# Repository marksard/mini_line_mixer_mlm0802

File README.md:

# Mini Line Mixer MLM0802

'Mini Line Mixer MLM0802' is 100mm x 100mm size audio line level mixer.  
A total of 3ch x2 of mono inputs and 1ch of stereo inupt, 2ch of stereo outputs are provided.  
This is perfect for mixing audio from small instruments.  
It does not have a pan pot, but can be used as a stereo 4-channel mixer.  

[blog](https://marksard.github.io/2023/02/23/make-line-mixer/)

## Specification

### Input

Monoral:  

- 3ch (A line group)  
- 3ch (B line group)  

3.5mm phone jack (TS, Unbaranced)

Stereo:  

- 1ch (Input as Tip to A line group, and as Ring to input B line group)  

3.5mm phone jack (TRS, Unbaranced)  

### Output

Monoral:  

- A output  
- B output  

3.5mm phone jack (TS, Unbaranced)  

Stereo:  

- Monitor output  

3.5mm phone jack (TRS, Unbaranced)  
The user can select A or B outputs for the left and right channels, respectively.  

### Power supply

- 5V to 9V
- MAX 100mA

### Block diagram

### Parts List

|Item|Qty|Reference(s)|Value|Part Model No.|
|:--|:--|:--|:--|:--|
|1|8|C1, C2, C3, C4, C5, C6, C7, C8|1u|サイズ max 5phi x 11mm|
|2|6|C9, C10, C12, C13, C15, C17|22p|セラミック seramic|
|3|2|C11, C14|47u|サイズ max 5phi x 11mm|
|4|2|C16, C18|470u|サイズ max 10phi x 12.5mm|
|5|1|C101|100u|サイズ max 10phi x 12.5mm|
|6|4|C102, C104, C105, C106|100n|積セラ multilayer ceramic|
|7|1|C103|47u|サイズ max 5phi x 11mm|
|8|1|J1|Ach1|マル信 est-marushin MJ-355W|
|9|1|J2|Ach2|マル信 est-marushin MJ-355W|
|10|1|J3|Ach3|マル信 est-marushin MJ-355W|
|11|1|J4|A/Bch4|マル信 est-marushin MJ-355W|
|12|1|J5|Bch1|マル信 est-marushin MJ-355W|
|13|1|J6|Bch2|マル信 est-marushin MJ-355W|
|14|1|J7|Bch3|マル信 est-marushin MJ-355W|
|15|1|J9|A Out|マル信 est-marushin MJ-355W|
|16|1|J10|B Out|マル信 est-marushin MJ-355W|
|17|1|J11|Phone Out|マル信 est-marushin MJ-355W|
|18|1|J101|Center negative|マル信 est-marushin MJ-179P|
|19|4|Q1, Q2, Q3, Q4|2SK170 or 2SK303L|2SK170 or 2SK303L|
|20|12|R1, R2, R3, R4, R5, R6, R7, R8, R12, R18, R22, R27|51k|金属皮膜 metal film 1/4w|
|21|4|R9, R15, R21, R26|1meg|金属皮膜 metal film 1/4w|
|22|4|R10, R11, R16, R17|27k|金属皮膜 metal film 1/4w|
|23|4|R14, R20, R25, R30|10k|金属皮膜 metal film 1/4w|
|24|2|R23, R28|20k|金属皮膜 metal film 1/4w|
|25|1|R101|1.5k|金属皮膜 metal film 1/4w|
|26|2|R102, R103|4.7k|金属皮膜 metal film 1/4w|
|27|6|RV1, RV2, RV3, RV5, RV6, RV7|A10k|ALPS RK09L1140-F15-C0-A103|
|28|1|RV4|A10k|ALPS RK09L1240-F15-C0-A103 2gang (2連)|
|29|2|RV9, RV10|B100k|ALPS RK09L1140-F15-C0-B104|
|30|1|RV11|B50k|ALPS RK09L1240-F15-C0-B503 2gang (2連)|
|31|1|SW1|Lch Selecter|NKK B-12CCPR|
|32|1|SW2|Rch Selecter|NKK B-12CCPR|
|33|1|SW101|Power Sw|NKK B-12CCPR|
|34|1|U1|NJM5532|NJM-5532|
|35|2|U2, U3|NJM5532|NJM-5532|
|36|4|-|-|Both Screw Spacer M3 11mm|
|37|8|-|-|Screw M3 4mm|
|38|4|-|-|Feet|
|39|10|-|Pot Knob|D-type 180digree<br>max outer size phi14mm|
|40|1|-|-|DC Adapter 9V 100mA Center negative, 2.1mm/5.5mm Jack|

### PCB image

### Schematic

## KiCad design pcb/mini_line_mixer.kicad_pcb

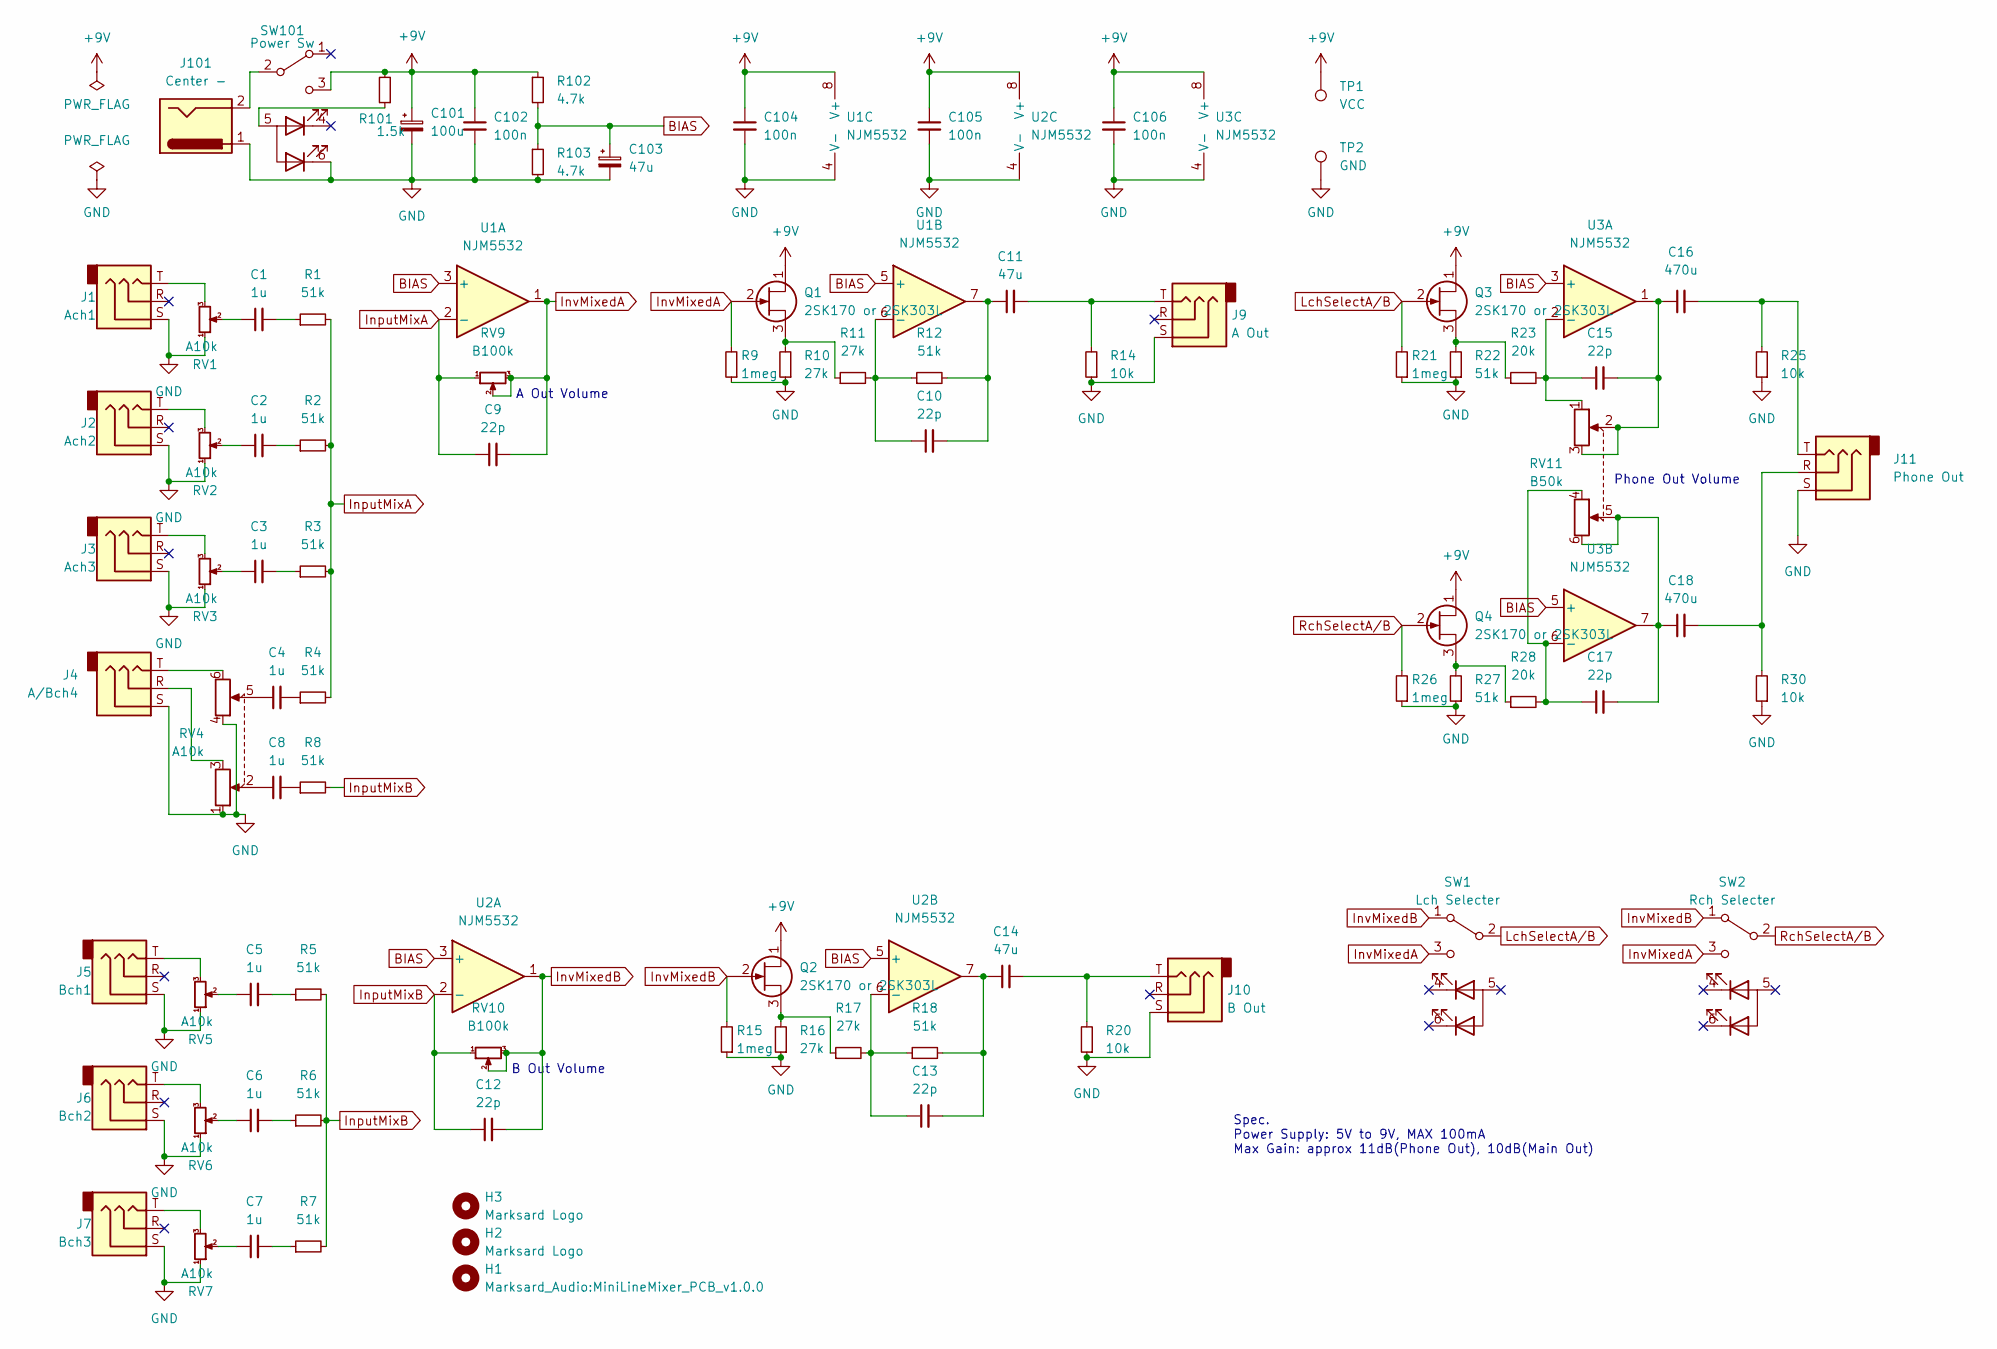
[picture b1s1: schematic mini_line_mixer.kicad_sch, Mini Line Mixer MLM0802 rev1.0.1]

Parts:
C1, C2, C3, C4, C5, C6, C7, C8: 1u; Capacitor_THT_5x11_Holizontal; Part Model No. サイズ max 5phi x 11mmまで
C9, C10, C12, C13, C15, C17: 22p; C_Disc_D4.7mm_W2.5mm_P5.00mm; Part Model No. セラミック seramic
C11, C14, C103: 47u; Capacitor_THT_5x11_Holizontal; Part Model No. サイズ max 5phi x 11mmまで
C16, C18: 470u; Capacitor_THT_10x12.5_Holizontal; Part Model No. サイズ max 10phi x 12.5mm
C101: 100u; Capacitor_THT_10x12.5_Holizontal; Part Model No. サイズ max 10phi x 12.5mm
C102, C104, C105, C106: 100n; Capacitor_THT_2.5_3.6_Ceramic; Part Model No. 積セラ multilayer ceramic
H1: Marksard_Audio:MiniLineMixer_PCB_v1.0.0; MiniLineMixer_PCB_v1.0.0
H2, H3: Marksard Logo; marksard_logo
J1: Ach1; MJ-355W; Part Model No. マル信 est-marushin MJ-355W
J2: Ach2; MJ-355W; Part Model No. マル信 est-marushin MJ-355W
J3: Ach3; MJ-355W; Part Model No. マル信 est-marushin MJ-355W
J4: A/Bch4; MJ-355W; Part Model No. マル信 est-marushin MJ-355W
J5: Bch1; MJ-355W; Part Model No. マル信 est-marushin MJ-355W
J6: Bch2; MJ-355W; Part Model No. マル信 est-marushin MJ-355W
J7: Bch3; MJ-355W; Part Model No. マル信 est-marushin MJ-355W
J9: A Out; MJ-355W; Part Model No. マル信 est-marushin MJ-355W
J10: B Out; MJ-355W; Part Model No. マル信 est-marushin MJ-355W
J11: Phone Out; MJ-355W; Part Model No. マル信 est-marushin MJ-355W
J101: Center -; MJ-179P; Part Model No. マル信 est-marushin MJ-179P
Q1, Q2, Q3, Q4: 2SK170 or 2SK303L; TO-92_K170-303L; Part Model No. 2SK170 or 2SK303L
R1, R2, R3, R4, R5, R6, R7, R8, R12, R18, R22, R27: 51k; R_Axial_DIN0204_L3.6mm_D1.6mm_P2.54mm_Vertical; Part Model No. 金属皮膜 metal film 1/4w
R9, R15, R21, R26: 1meg; R_Axial_DIN0204_L3.6mm_D1.6mm_P2.54mm_Vertical; Part Model No. 金属皮膜 metal film 1/4w
R10, R11, R16, R17: 27k; R_Axial_DIN0204_L3.6mm_D1.6mm_P2.54mm_Vertical; Part Model No. 金属皮膜 metal film 1/4w
R14, R20, R25, R30: 10k; R_Axial_DIN0204_L3.6mm_D1.6mm_P2.54mm_Vertical; Part Model No. 金属皮膜 metal film 1/4w
R23, R28: 20k; R_Axial_DIN0204_L3.6mm_D1.6mm_P2.54mm_Vertical; Part Model No. 金属皮膜 metal film 1/4w
R101: 1.5k; R_Axial_DIN0204_L3.6mm_D1.6mm_P2.54mm_Vertical; Part Model No. 金属皮膜 metal film 1/4w
R102, R103: 4.7k; R_Axial_DIN0204_L3.6mm_D1.6mm_P2.54mm_Vertical; Part Model No. 金属皮膜 metal film 1/4w
RV1, RV2, RV3, RV5, RV6, RV7: A10k; Potentiometer_THT_RK09L1140; Part Model No. ALPS RK09L1140-F15-C0-A103
RV4: A10k; Potentiometer_THT_RK09L1240; Part Model No. ALPS RK09L1240-F15-C0-A103(2連)
RV9, RV10: B100k; Potentiometer_THT_RK09L1140; Part Model No. ALPS RK09L1140-F15-C0-B104
RV11: B50k; Potentiometer_THT_RK09L1240; Part Model No. ALPS RK09L1240-F15-C0-B503(2連)
SW1: Lch Selecter; B-12CCPR; Part Model No. NKK B-12CCPR
SW2: Rch Selecter; B-12CCPR; Part Model No. NKK B-12CCPR
SW101: Power Sw; B-12CCPR; Part Model No. NKK B-12CCPRM
TP1: VCC; TestPoint_THTPad_D1.5mm_Drill0.7mm
TP2: GND; TestPoint_THTPad_D1.5mm_Drill0.7mm
U1, U2, U3: NJM5532; DIP-8_W7.62mm_Socket; Part Model No. NJM-5532

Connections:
+9V: C101.1, C102.1, C104.1, C105.1, C106.1, Q1.1 (D), Q2.1 (D), Q3.1 (D), Q4.1 (D), R101.2, R102.1, SW101.3 (C), TP1.1, U1.8 (V+), U2.8 (V+), U3.8 (V+)
BIAS: C103.1, R102.2, R103.1, U1.3 (+), U1.5 (+), U2.3 (+), U2.5 (+), U3.3 (+), U3.5 (+)
GND: C101.2, C102.2, C103.2, C104.2, C105.2, C106.2, J1.S, J2.S, J3.S, J4.S, J5.S, J6.S, J7.S, J9.S, J10.S, J11.S, J101.1, R9.1, R10.1, R14.1, R15.1, R16.1, R20.1, R21.1, R22.1, R25.1, R26.1, R27.1, R30.1, R103.2, RV1.1, RV1.MP, RV2.1, RV2.MP, RV3.1, RV3.MP, RV4.1, RV4.4, RV4.MP, RV5.1, RV5.MP, RV6.1, RV6.MP, RV7.1, RV7.MP, RV9.MP, RV10.MP, RV11.MP, SW101.6 (F), TP2.1, U1.4 (V-), U2.4 (V-), U3.4 (V-)
InputMixA: C9.1, R1.2, R2.2, R3.2, R4.2, RV9.1, U1.2 (-)
InputMixB: C12.1, R5.2, R6.2, R7.2, R8.2, RV10.1, U2.2 (-)
InvMixedA: C9.2, Q1.2 (G), R9.2, RV9.2, RV9.3, SW1.3 (C), SW2.3 (C), U1.1
InvMixedB: C12.2, Q2.2 (G), R15.2, RV10.2, RV10.3, SW1.1 (A), SW2.1 (A), U2.1
LchSelectA/B: Q3.2 (G), R21.2, SW1.2 (B)
unnamed: C1.1, RV1.2
unnamed: C1.2, R1.1
unnamed: C2.1, RV2.2
unnamed: C2.2, R2.1
unnamed: C3.1, RV3.2
unnamed: C3.2, R3.1
unnamed: C4.1, RV4.5
unnamed: C4.2, R4.1
unnamed: C5.1, RV5.2
unnamed: C5.2, R5.1
unnamed: C6.1, RV6.2
unnamed: C6.2, R6.1
unnamed: C7.1, RV7.2
unnamed: C7.2, R7.1
unnamed: C8.1, RV4.2
unnamed: C8.2, R8.1
unnamed: C10.1, R11.2, R12.1, U1.6 (-)
unnamed: C10.2, C11.1, R12.2, U1.7
unnamed: C11.2, J9.T, R14.2
unnamed: C13.1, R17.2, R18.1, U2.6 (-)
unnamed: C13.2, C14.1, R18.2, U2.7
unnamed: C14.2, J10.T, R20.2
unnamed: C15.1, R23.2, RV11.1, U3.2 (-)
unnamed: C15.2, C16.1, RV11.2, RV11.3, U3.1
unnamed: C16.2, J11.T, R25.2
unnamed: C17.1, R28.2, RV11.4, U3.6 (-)
unnamed: C17.2, C18.1, RV11.5, RV11.6, U3.7
unnamed: C18.2, J11.R, R30.2
unnamed: J1.T, RV1.3
unnamed: J2.T, RV2.3
unnamed: J3.T, RV3.3
unnamed: J4.R, RV4.3
unnamed: J4.T, RV4.6
unnamed: J5.T, RV5.3
unnamed: J6.T, RV6.3
unnamed: J7.T, RV7.3
unnamed: J101.2, SW101.2 (B)
unnamed: Q1.3 (S), R10.2, R11.1
unnamed: Q2.3 (S), R16.2, R17.1
unnamed: Q3.3 (S), R22.2, R23.1
unnamed: Q4.3 (S), R27.2, R28.1
unnamed: R101.1, SW101.5 (E)
RchSelectA/B: Q4.2 (G), R26.2, SW2.2 (B)

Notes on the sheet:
Phone Out Volume
A Out Volume
B Out Volume
Spec. Power Supply: 5V to 9V, MAX 100mA Max Gain: approx 11dB(Phone Out), 10dB(Main Out)

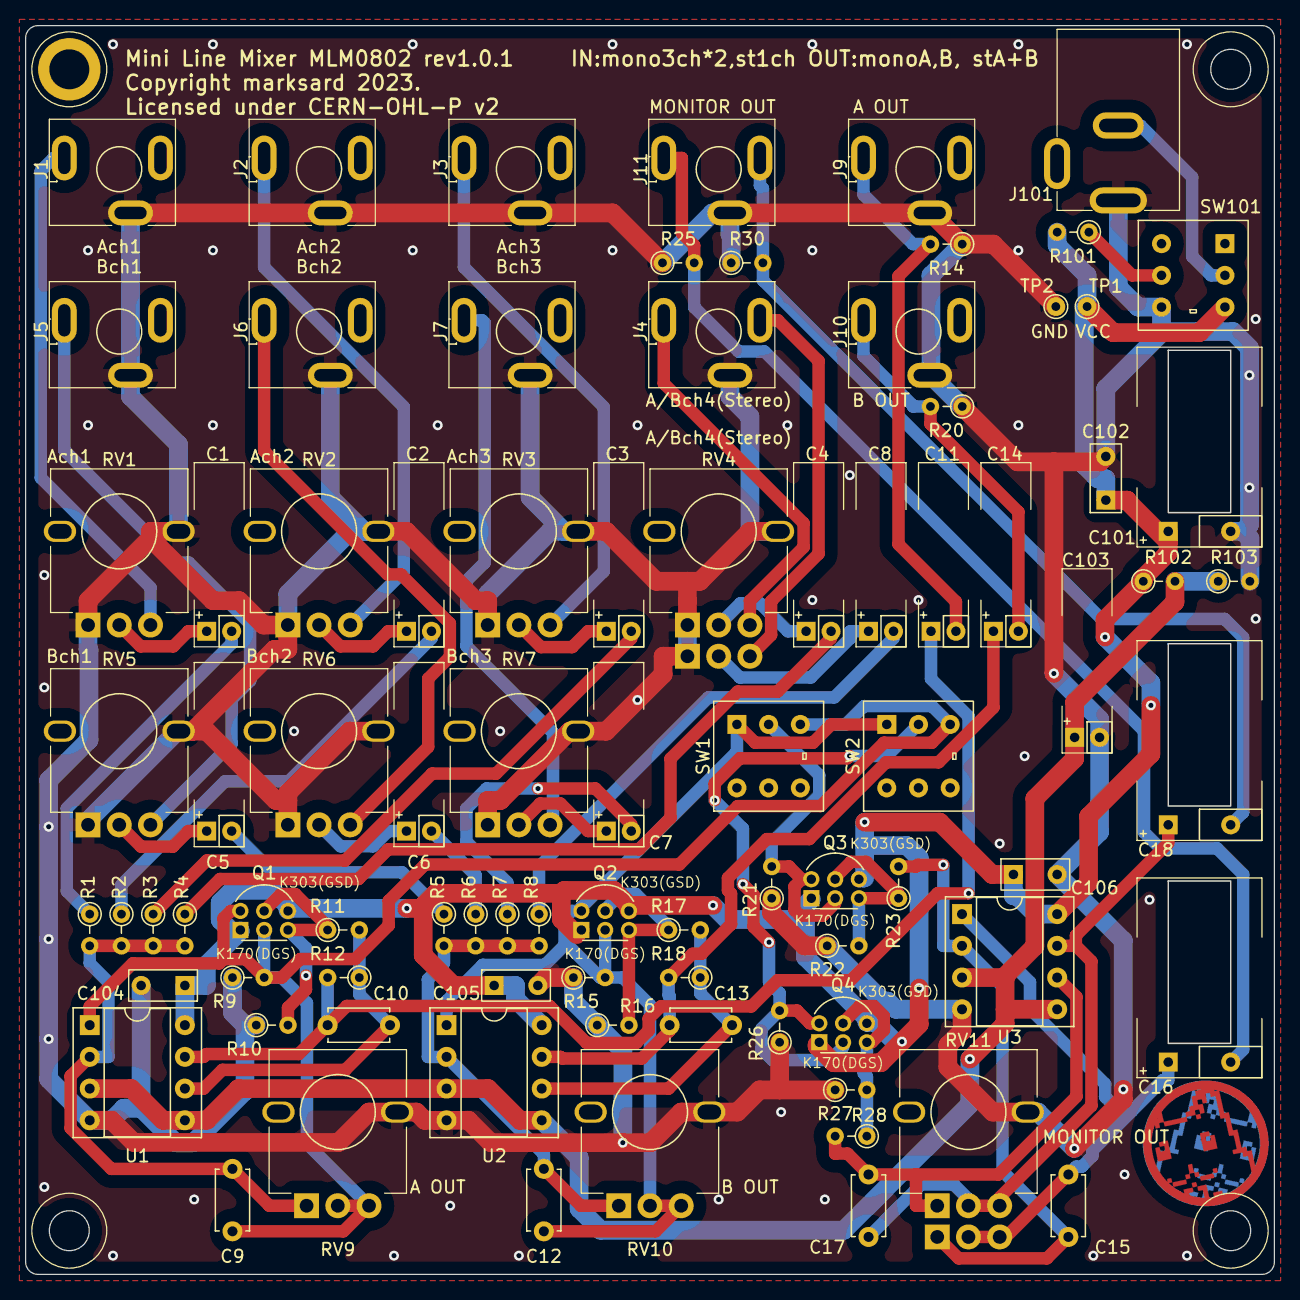
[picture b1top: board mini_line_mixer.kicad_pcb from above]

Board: 2 copper layers, 100.0 x 100.0 mm, 89 parts (1 on the bottom side), 51 nets.

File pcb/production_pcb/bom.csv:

Designator,Footprint,Quantity,Value,LCSC Part #
"C1, C2, C3, C4, C5, C6, C7, C8",Capacitor_THT_5x11_Holizontal,8,1u,
"C10, C12, C13, C15, C17, C9",C_Disc_D4.7mm_W2.5mm_P5.00mm,6,22p,
C101,Capacitor_THT_10x12.5_Holizontal,1,100u,
"C102, C104, C105, C106",Capacitor_THT_2.5_3.6_Ceramic,4,100n,
"C103, C11, C14",Capacitor_THT_5x11_Holizontal,3,47u,
"C16, C18",Capacitor_THT_10x12.5_Holizontal,2,470u,
H1,MiniLineMixer_PCB_v1.0.0,1,Marksard_Audio:MiniLineMixer_PCB_v1.0.0,
"H2, H3",marksard_logo,2,Marksard Logo,
J1,MJ-355W,1,Ach1,
J10,MJ-355W,1,B Out,
J101,MJ-179P,1,Center -,
J11,MJ-355W,1,Phone Out,
J2,MJ-355W,1,Ach2,
J3,MJ-355W,1,Ach3,
J4,MJ-355W,1,A/Bch4,
J5,MJ-355W,1,Bch1,
J6,MJ-355W,1,Bch2,
J7,MJ-355W,1,Bch3,
J9,MJ-355W,1,A Out,
"Q1, Q2, Q3, Q4",TO-92_K170-303L,4,2SK170 or 2SK303L,
"R1, R12, R18, R2, R22, R27, R3, R4, R5, R6, R7, R8",R_Axial_DIN0204_L3.6mm_D1.6mm_P2.54mm_Vertical,12,51k,
"R10, R11, R16, R17",R_Axial_DIN0204_L3.6mm_D1.6mm_P2.54mm_Vertical,4,27k,
R101,R_Axial_DIN0204_L3.6mm_D1.6mm_P2.54mm_Vertical,1,1.5k,
"R102, R103",R_Axial_DIN0204_L3.6mm_D1.6mm_P2.54mm_Vertical,2,4.7k,
"R14, R20, R25, R30",R_Axial_DIN0204_L3.6mm_D1.6mm_P2.54mm_Vertical,4,10k,
"R15, R21, R26, R9",R_Axial_DIN0204_L3.6mm_D1.6mm_P2.54mm_Vertical,4,1meg,
"R23, R28",R_Axial_DIN0204_L3.6mm_D1.6mm_P2.54mm_Vertical,2,20k,
"RV1, RV2, RV3, RV5, RV6, RV7",Potentiometer_THT_RK09L1140,6,A10k,
"RV10, RV9",Potentiometer_THT_RK09L1140,2,B100k,
RV11,Potentiometer_THT_RK09L1240,1,B50k,
RV4,Potentiometer_THT_RK09L1240,1,A10k,
SW1,B-12CCPR,1,Lch Selecter,
SW101,B-12CCPR,1,Power Sw,
SW2,B-12CCPR,1,Rch Selecter,
TP1,TestPoint_THTPad_D1.5mm_Drill0.7mm,1,VCC,
TP2,TestPoint_THTPad_D1.5mm_Drill0.7mm,1,GND,
"U1, U2, U3",DIP-8_W7.62mm_Socket,3,NJM5532,

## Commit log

2023-03-01 first time
2023-03-02 move folder
2023-03-02 Fixed parts discription
2023-03-02 add bloack diagram
2023-03-07 add gitignore

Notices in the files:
pcb/mini_line_mixer.kicad_pcb:
Licensed under CERN-OHL-P v2
